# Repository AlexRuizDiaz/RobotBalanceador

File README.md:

Robot balanceador de PSM2
Requisitos:
- Kicad 8.0.4 o mayor
- STM32CubeIDE 1.14.0 o mayor

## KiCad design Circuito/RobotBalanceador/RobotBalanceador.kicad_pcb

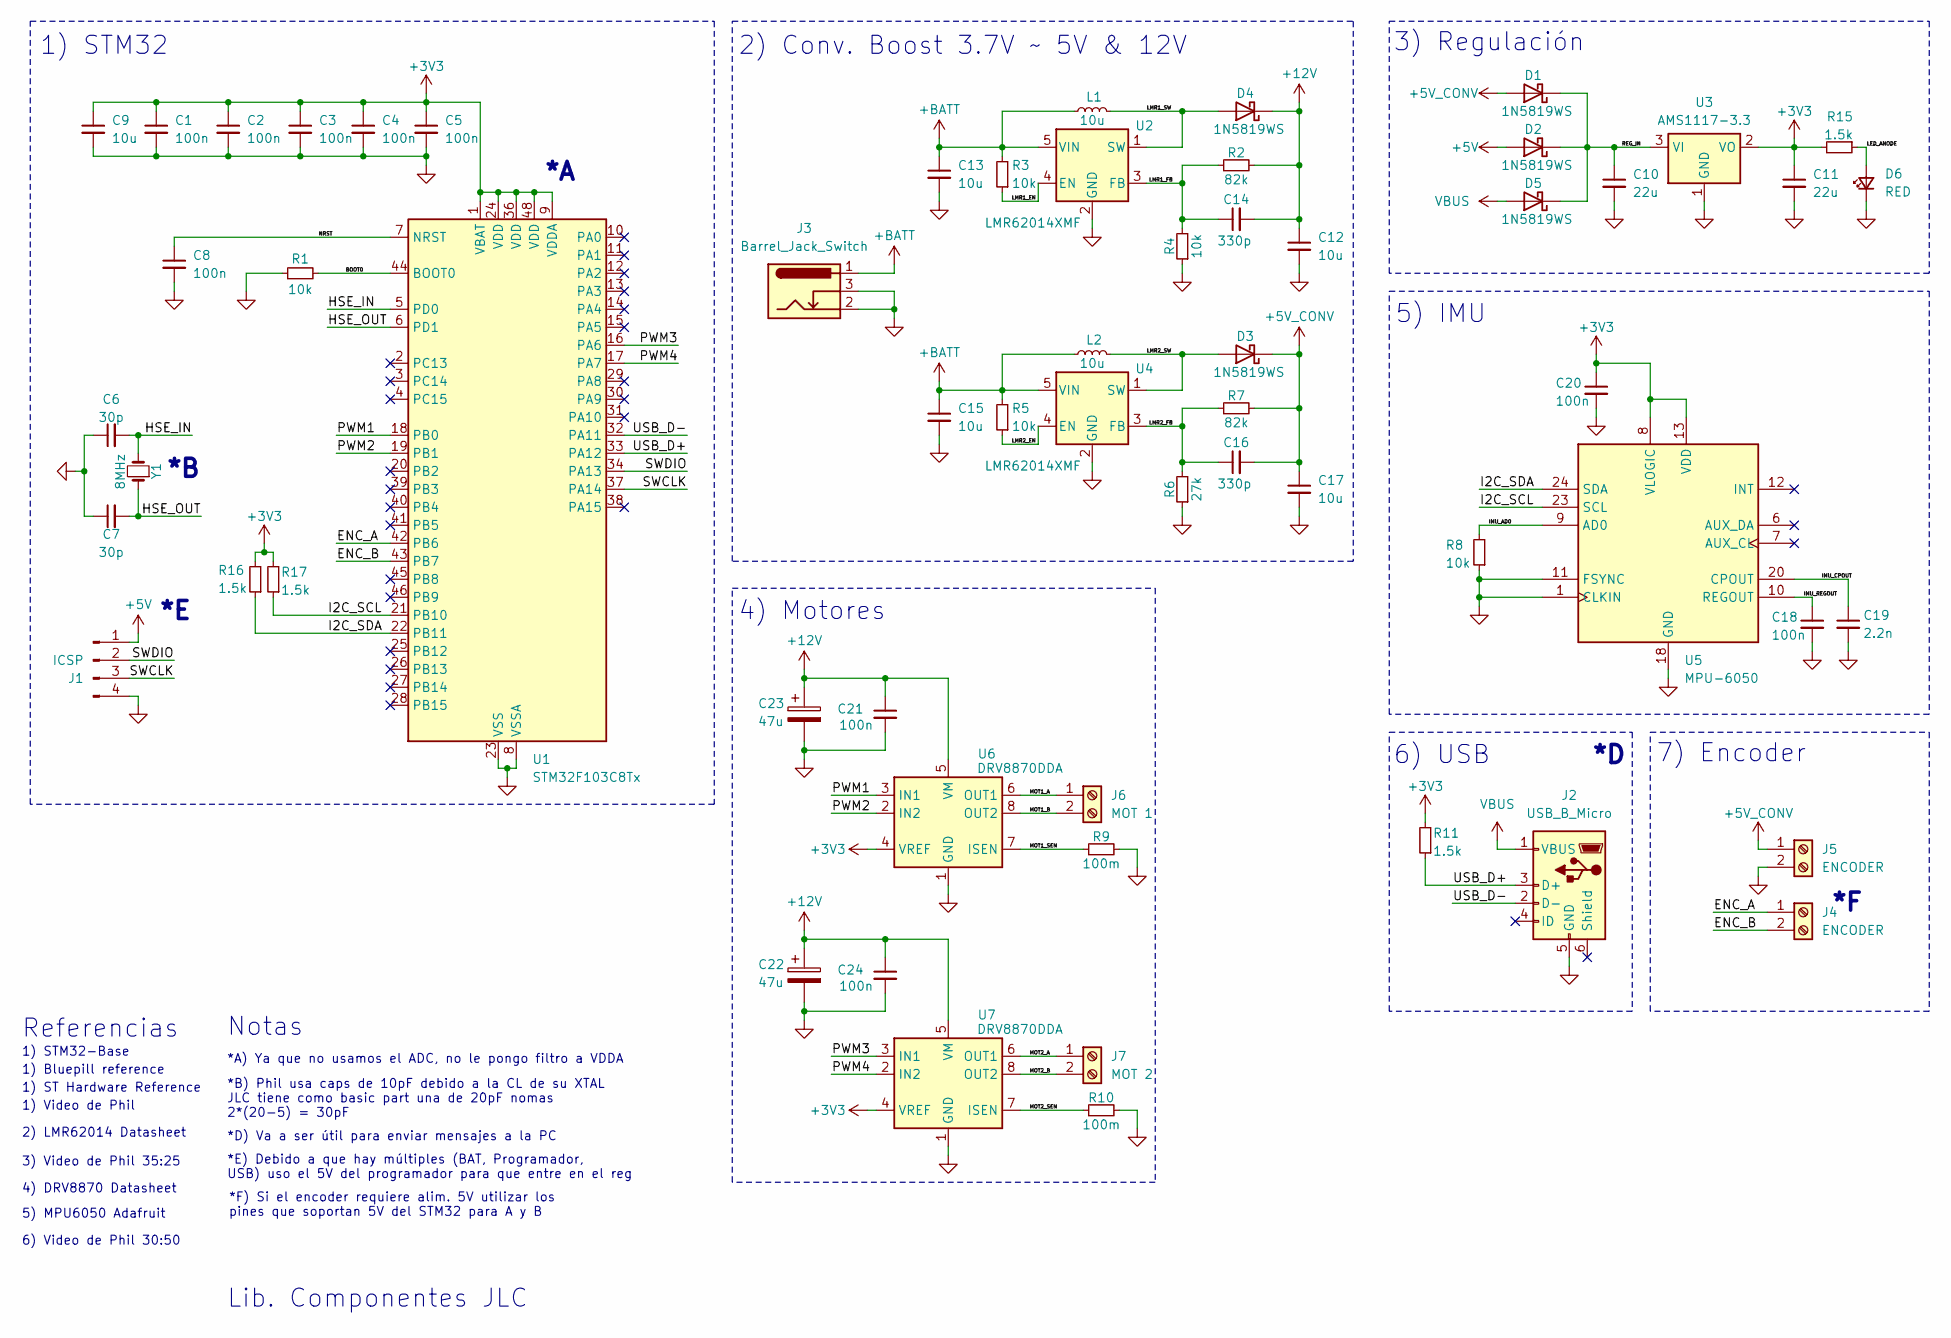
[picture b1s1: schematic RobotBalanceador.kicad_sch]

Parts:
C1, C2, C3, C4, C5, C8, C18, C20, C21, C24: 100n; C_0603_1608Metric; LCSC C14663
C6: 30p; C_0603_1608Metric; LCSC C1658
C7: 30p; C_0603_1608Metric; LCSC C1648
C9, C12, C13, C15, C17: 10u; C_0603_1608Metric; LCSC C19702
C10, C11: 22u; C_0805_2012Metric; LCSC C45783
C14, C16: 330p; C_0603_1608Metric; LCSC C1664
C19: 2.2n; C_0603_1608Metric; LCSC C1604
C22, C23: 47u; CP_Elec_6.3x5.4; LCSC C2836440
D1, D2, D3, D4, D5: 1N5819WS; D_SOD-323; LCSC C191023
D6: RED; LED_0603_1608Metric; LCSC C2286
J1: ICSP; PinHeader_1x04_P2.54mm_Vertical; LCSC C6332197
J2: USB_B_Micro; USB_Micro-B_Molex_47346-0001; LCSC C132560
J3: Barrel_Jack_Switch; BarrelJack_GCT_DCJ200-10-A_Horizontal; LCSC C5280493
J4, J5: ENCODER; TerminalBlock_bornier-2_P5.08mm; LCSC C474906
J6: MOT 1; TerminalBlock_bornier-2_P5.08mm; LCSC C474906
J7: MOT 2; TerminalBlock_bornier-2_P5.08mm; LCSC C474906
L1, L2: 10u; L_1008_2520Metric; LCSC C602018
R1, R3, R4, R5, R8: 10k; R_0603_1608Metric; LCSC C25804
R2, R7: 82k; R_0603_1608Metric; LCSC C23254
R6: 27k; R_0603_1608Metric; LCSC C22967
R9, R10: 100m; R_1206_3216Metric; LCSC C25334
R11, R15, R16, R17: 1.5k; R_0603_1608Metric; LCSC C22843
U1: STM32F103C8Tx; LQFP-48_7x7mm_P0.5mm; LCSC C8734
U2, U4: LMR62014XMF; SOT-23-5; LCSC C55182
U3: AMS1117-3.3; SOT-223-3_TabPin2; LCSC C6186
U5: MPU-6050; InvenSense_QFN-24_4x4mm_P0.5mm; LCSC C24112
U6, U7: DRV8870DDA; Texas_HTSOP-8-1EP_3.9x4.9mm_P1.27mm_EP2.95x4.9mm_Mask2.4x3.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; LCSC C86590
Y1: 8MHz; Crystal_SMD_5032-2Pin_5.0x3.2mm; LCSC C115962

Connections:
+3V3: C1.1, C2.1, C3.1, C4.1, C5.1, C9.1, C11.1, C20.1, R11.2, R15.2, R16.2, R17.2, U1.1 (VBAT), U1.9 (VDDA), U1.24 (VDD), U1.36 (VDD), U1.48 (VDD), U3.2 (VO), U5.8 (VLOGIC), U5.13 (VDD), U6.4 (VREF), U7.4 (VREF)
+5V: D2.2 (A), J1.1
+5V_CONV: C16.2, C17.1, D1.2 (A), D3.1 (K), J5.1, R7.2
+12V: C12.1, C14.2, C21.1, C22.1, C23.1, C24.1, D4.1 (K), R2.2, U6.5 (VM), U7.5 (VM)
+BATT: C13.1, C15.1, J3.1, L1.1, L2.1, R3.2, R5.2, U2.5 (VIN), U4.5 (VIN)
/BOOT0: R1.2, U1.44 (BOOT0)
/ENC_A: J4.1, U1.42 (PB6)
/ENC_B: J4.2, U1.43 (PB7)
/HSE_IN: C6.2, U1.5 (PD0), Y1.2
/HSE_OUT: C7.2, U1.6 (PD1), Y1.1
/I2C_SCL: R17.1, U1.21 (PB10), U5.23 (SCL)
/I2C_SDA: R16.1, U1.22 (PB11), U5.24 (SDA)
/IMU_AD0: R8.2, U5.9 (AD0)
/IMU_CPOUT: C19.1, U5.20 (CPOUT)
/IMU_REGOUT: C18.1, U5.10 (REGOUT)
/LED_ANODE: D6.2 (A), R15.1
/LMR1_EN: R3.1, U2.4 (EN)
/LMR1_FB: C14.1, R2.1, R4.2, U2.3 (FB)
/LMR1_SW: D4.2 (A), L1.2, U2.1 (SW)
/LMR2_EN: R5.1, U4.4 (EN)
/LMR2_FB: C16.1, R6.2, R7.1, U4.3 (FB)
/LMR2_SW: D3.2 (A), L2.2, U4.1 (SW)
/MOT1_A: J6.1, U6.6 (OUT1)
/MOT1_B: J6.2, U6.8 (OUT2)
/MOT1_SEN: R9.1, U6.7 (ISEN)
/MOT2_A: J7.1, U7.6 (OUT1)
/MOT2_B: J7.2, U7.8 (OUT2)
/MOT2_SEN: R10.1, U7.7 (ISEN)
/NRST: C8.1, U1.7 (NRST)
/PWM1: U1.18 (PB0), U6.3 (IN1)
/PWM2: U1.19 (PB1), U6.2 (IN2)
/PWM3: U1.16 (PA6), U7.3 (IN1)
/PWM4: U1.17 (PA7), U7.2 (IN2)
/REG_IN: C10.1, D1.1 (K), D2.1 (K), D5.1 (K), U3.3 (VI)
/SWCLK: J1.3, U1.37 (PA14)
/SWDIO: J1.2, U1.34 (PA13)
/USB_D+: J2.3 (D+), R11.1, U1.33 (PA12)
/USB_D-: J2.2 (D-), U1.32 (PA11)
GND: C1.2, C2.2, C3.2, C4.2, C5.2, C6.1, C7.1, C8.2, C9.2, C10.2, C11.2, C12.2, C13.2, C15.2, C17.2, C18.2, C19.2, C20.2, C21.2, C22.2, C23.2, C24.2, D6.1 (K), J1.4, J2.5 (GND), J3.2, J3.3, J5.2, R1.1, R4.1, R6.1, R8.1, R9.2, R10.2, U1.8 (VSSA), U1.23 (VSS), U1.35 (VSS), U1.47 (VSS), U2.2 (GND), U3.1 (GND), U4.2 (GND), U5.1 (CLKIN), U5.11 (FSYNC), U5.18 (GND), U6.1 (GND), U6.9 (GND), U7.1 (GND), U7.9 (GND)
VBUS: D5.2 (A), J2.1 (VBUS)

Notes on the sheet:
Lib. Componentes JLC
1) Bluepill reference
1) STM32-Base
4) DRV8870 Datasheet
*A) Ya que no usamos el ADC, no le pongo filtro a VDDA
*B) Phil usa caps de 10pF debido a la CL de su XTAL JLC tiene como basic part una de 20pF nomas 2*(20-5) = 30pF
*F) Si el encoder requiere alim. 5V utilizar los pines que soportan 5V del STM32 para A y B
6) USB
7) Encoder
5) MPU6050 Adafruit
3) Regulación
*E) Debido a que hay múltiples (BAT, Programador, USB) uso el 5V del programador para que entre en el reg
2) LMR62014 Datasheet
1) ST Hardware Reference
4) Motores
3) Video de Phil 35:25
Referencias
*D) Va a ser útil para enviar mensajes a la PC
1) STM32
1) Video de Phil
2) Conv. Boost 3.7V ~ 5V & 12V
5) IMU
6) Video de Phil 30:50
Notas

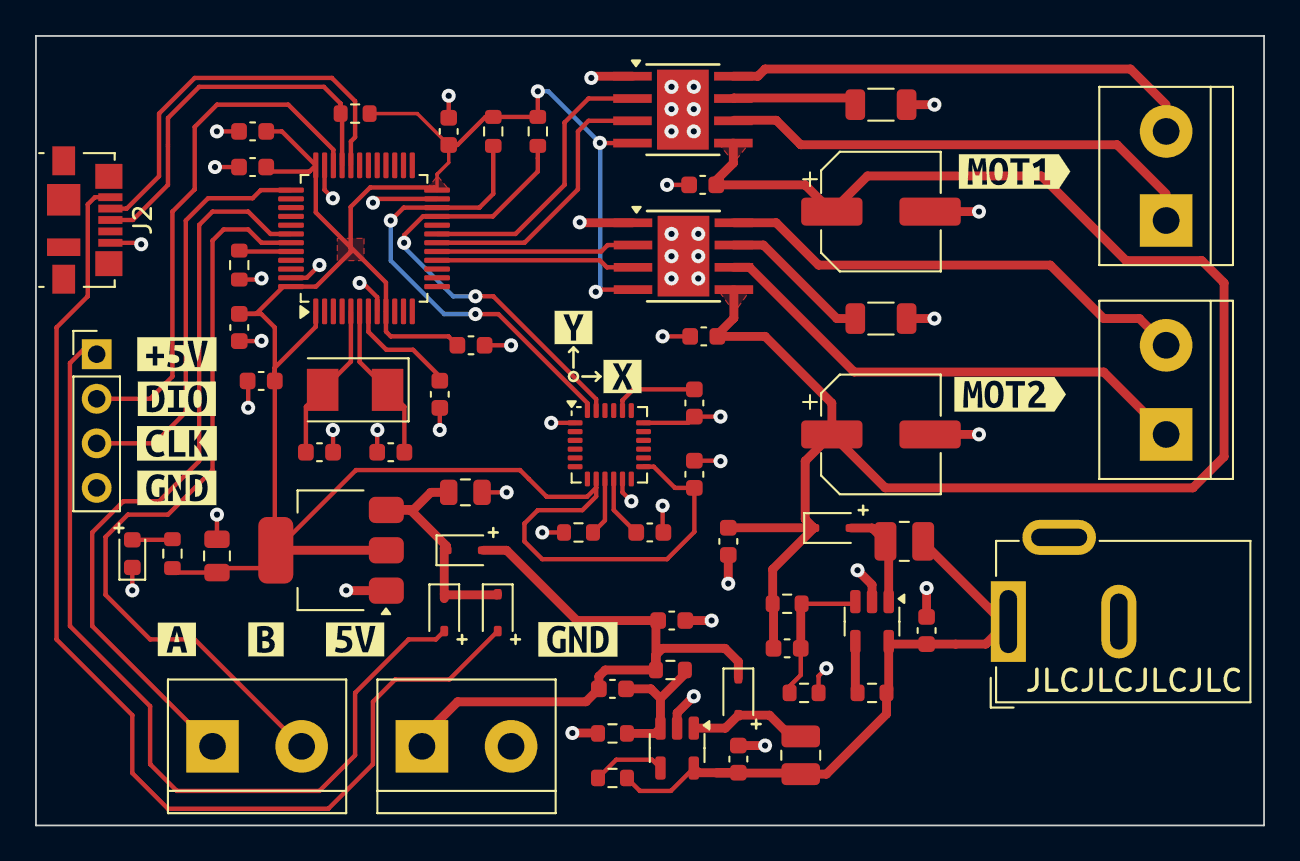
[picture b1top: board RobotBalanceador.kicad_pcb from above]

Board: 2 copper layers, 70.0 x 45.0 mm, 73 parts (0 on the bottom side), 40 nets.

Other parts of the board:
kibuzzard-66D67A2F: G***; kibuzzard-66D67A2F
kibuzzard-66D67A08: G***; kibuzzard-66D67A08
kibuzzard-66D67A11: G***; kibuzzard-66D67A11
kibuzzard-66D67A48: G***; kibuzzard-66D67A48
kibuzzard-66D67A51: G***; kibuzzard-66D67A51
kibuzzard-66D67A84: G***; kibuzzard-66D67A84
kibuzzard-66D67EE6: G***; kibuzzard-66D67EE6
kibuzzard-66D67F1F: G***; kibuzzard-66D67F1F
kibuzzard-66D679E5: G***; kibuzzard-66D679E5
kibuzzard-66D679E8: G***; kibuzzard-66D679E8
kibuzzard-66D679EB: G***; kibuzzard-66D679EB
kibuzzard-66D679FF: G***; kibuzzard-66D679FF

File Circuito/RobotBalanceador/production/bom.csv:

Designator,Footprint,Quantity,Value,LCSC Part #
"C1, C18, C2, C20, C21, C24, C3, C4, C5, C8",0603,10,100n,C14663
"C10, C11",0805,2,22u,C45783
"C12, C13, C15, C17, C9",0603,5,10u,C19702
"C14, C16",0603,2,330p,C1664
C19,0603,1,2.2n,C1604
"C22, C23",CP_Elec_6.3x5.4,2,47u,C2836440
C6,0603,1,30p,C1658
C7,0603,1,30p,C1648
"D1, D2, D3, D4, D5",D_SOD-323,5,1N5819WS,C191023
D6,0603,1,RED,C2286
J1,PinHeader_1x04_P2.54mm_Vertical,1,ICSP,C6332197
J2,USB_Micro-B_Molex_47346-0001,1,USB_B_Micro,C132560
J3,BarrelJack_GCT_DCJ200-10-A_Horizontal,1,Barrel_Jack_Switch,C5280493
"J4, J5",TerminalBlock_bornier-2_P5.08mm,2,ENCODER,C474906
J6,TerminalBlock_bornier-2_P5.08mm,1,MOT 1,C474906
J7,TerminalBlock_bornier-2_P5.08mm,1,MOT 2,C474906
"L1, L2",1008,2,10u,C602018
"R1, R3, R4, R5, R8",0603,5,10k,C25804
"R10, R9",1206,2,100m,C25334
"R11, R15, R16, R17",0603,4,1.5k,C22843
"R2, R7",0603,2,82k,C23254
R6,0603,1,27k,C22967
U1,LQFP-48_7x7mm_P0.5mm,1,STM32F103C8Tx,C8734
"U2, U4",SOT-23-5,2,LMR62014XMF,C55182
U3,SOT-223-3_TabPin2,1,AMS1117-3.3, C6186
U5,InvenSense_QFN-24_4x4mm_P0.5mm,1,MPU-6050,C24112
"U6, U7",Texas_HTSOP-8-1EP_3.9x4.9mm_P1.27mm_EP2.95x4.9mm_Mask2.4x3.1mm_ThermalVias,2,DRV8870DDA,C86590
Y1,Crystal_SMD_5032-2Pin_5.0x3.2mm,1,8MHz,C115962

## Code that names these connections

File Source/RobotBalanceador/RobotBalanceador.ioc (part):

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Mcu.Name=STM32F103C(8-B)Tx
Mcu.Package=LQFP48
Mcu.UserName=STM32F103C8Tx
PA11.Mode=Device
PA11.Signal=USB_DM
PA12.Mode=Device
PA12.Signal=USB_DP
PA6.GPIOParameters=GPIO_Label
PA6.GPIO_Label=PWM3
PA6.Signal=S_TIM3_CH1
PA7.GPIOParameters=GPIO_Label
PA7.GPIO_Label=PWM4
PA7.Signal=S_TIM3_CH2
PB0.GPIOParameters=GPIO_Label
PB0.GPIO_Label=PWM1
PB0.Signal=S_TIM3_CH3
PB1.GPIOParameters=GPIO_Label
PB1.GPIO_Label=PWM2
PB1.Signal=S_TIM3_CH4
PB10.Mode=I2C
PB10.Signal=I2C2_SCL
PB11.Mode=I2C
PB11.Signal=I2C2_SDA
PB12.GPIOParameters=GPIO_Label
PB12.GPIO_Label=MOT1_IN1
PB12.Signal=GPIO_Output
PB13.GPIOParameters=GPIO_Label
PB13.GPIO_Label=MOT1_IN2
PB13.Signal=GPIO_Output
PB14.GPIOParameters=GPIO_Label
PB14.GPIO_Label=MOT2_IN1
PB14.Signal=GPIO_Output
PB15.GPIOParameters=GPIO_Label
PB15.GPIO_Label=MOT2_IN2
PB15.Signal=GPIO_Output
PB6.Signal=S_TIM4_CH1
PB7.Signal=S_TIM4_CH2
PB8.Signal=I2C1_SCL
PB9.Signal=I2C1_SDA
PD0-OSC_IN.Mode=HSE-External-Oscillator
PD0-OSC_IN.Signal=RCC_OSC_IN
PD1-OSC_OUT.Mode=HSE-External-Oscillator
PD1-OSC_OUT.Signal=RCC_OSC_OUT
RCC.SYSCLKFreq_VALUE=72000000
RCC.SYSCLKSource=RCC_SYSCLKSOURCE_PLLCLK
board=custom

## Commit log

2024-08-31 Estado Inicial
2024-08-31 Crear README.md
2024-08-31 Añadido circuitos boost, regulación y USB
2024-08-31 Añadido MPU6050
2024-08-31 Añadido conector para encoder y jack para batería
2024-08-31 Añadido puente H
2024-08-31 Referencias y textos ajustados
2024-08-31 Secciones ajustadas
2024-09-01 Añadido código/configuraciones para IMU y Encoder
2024-09-01 Se crea la funcion de direccion y asignacion PWM para los motores
2024-09-01 Asignados pines p/ motores y TIM2 PWM @1kHz
2024-09-01 Base para PID
2024-09-02 Reasig. de pines, TIM3 p/ PWM, I2C2 p/ IMU y Comps. colocados en PCB
2024-09-02 Ruteado inicial de tracks
2024-09-03 Ruteado completo, gerbers generados
2024-09-03 Modificaciones a USB y ruteado
2024-09-04 Añadida función de PID
